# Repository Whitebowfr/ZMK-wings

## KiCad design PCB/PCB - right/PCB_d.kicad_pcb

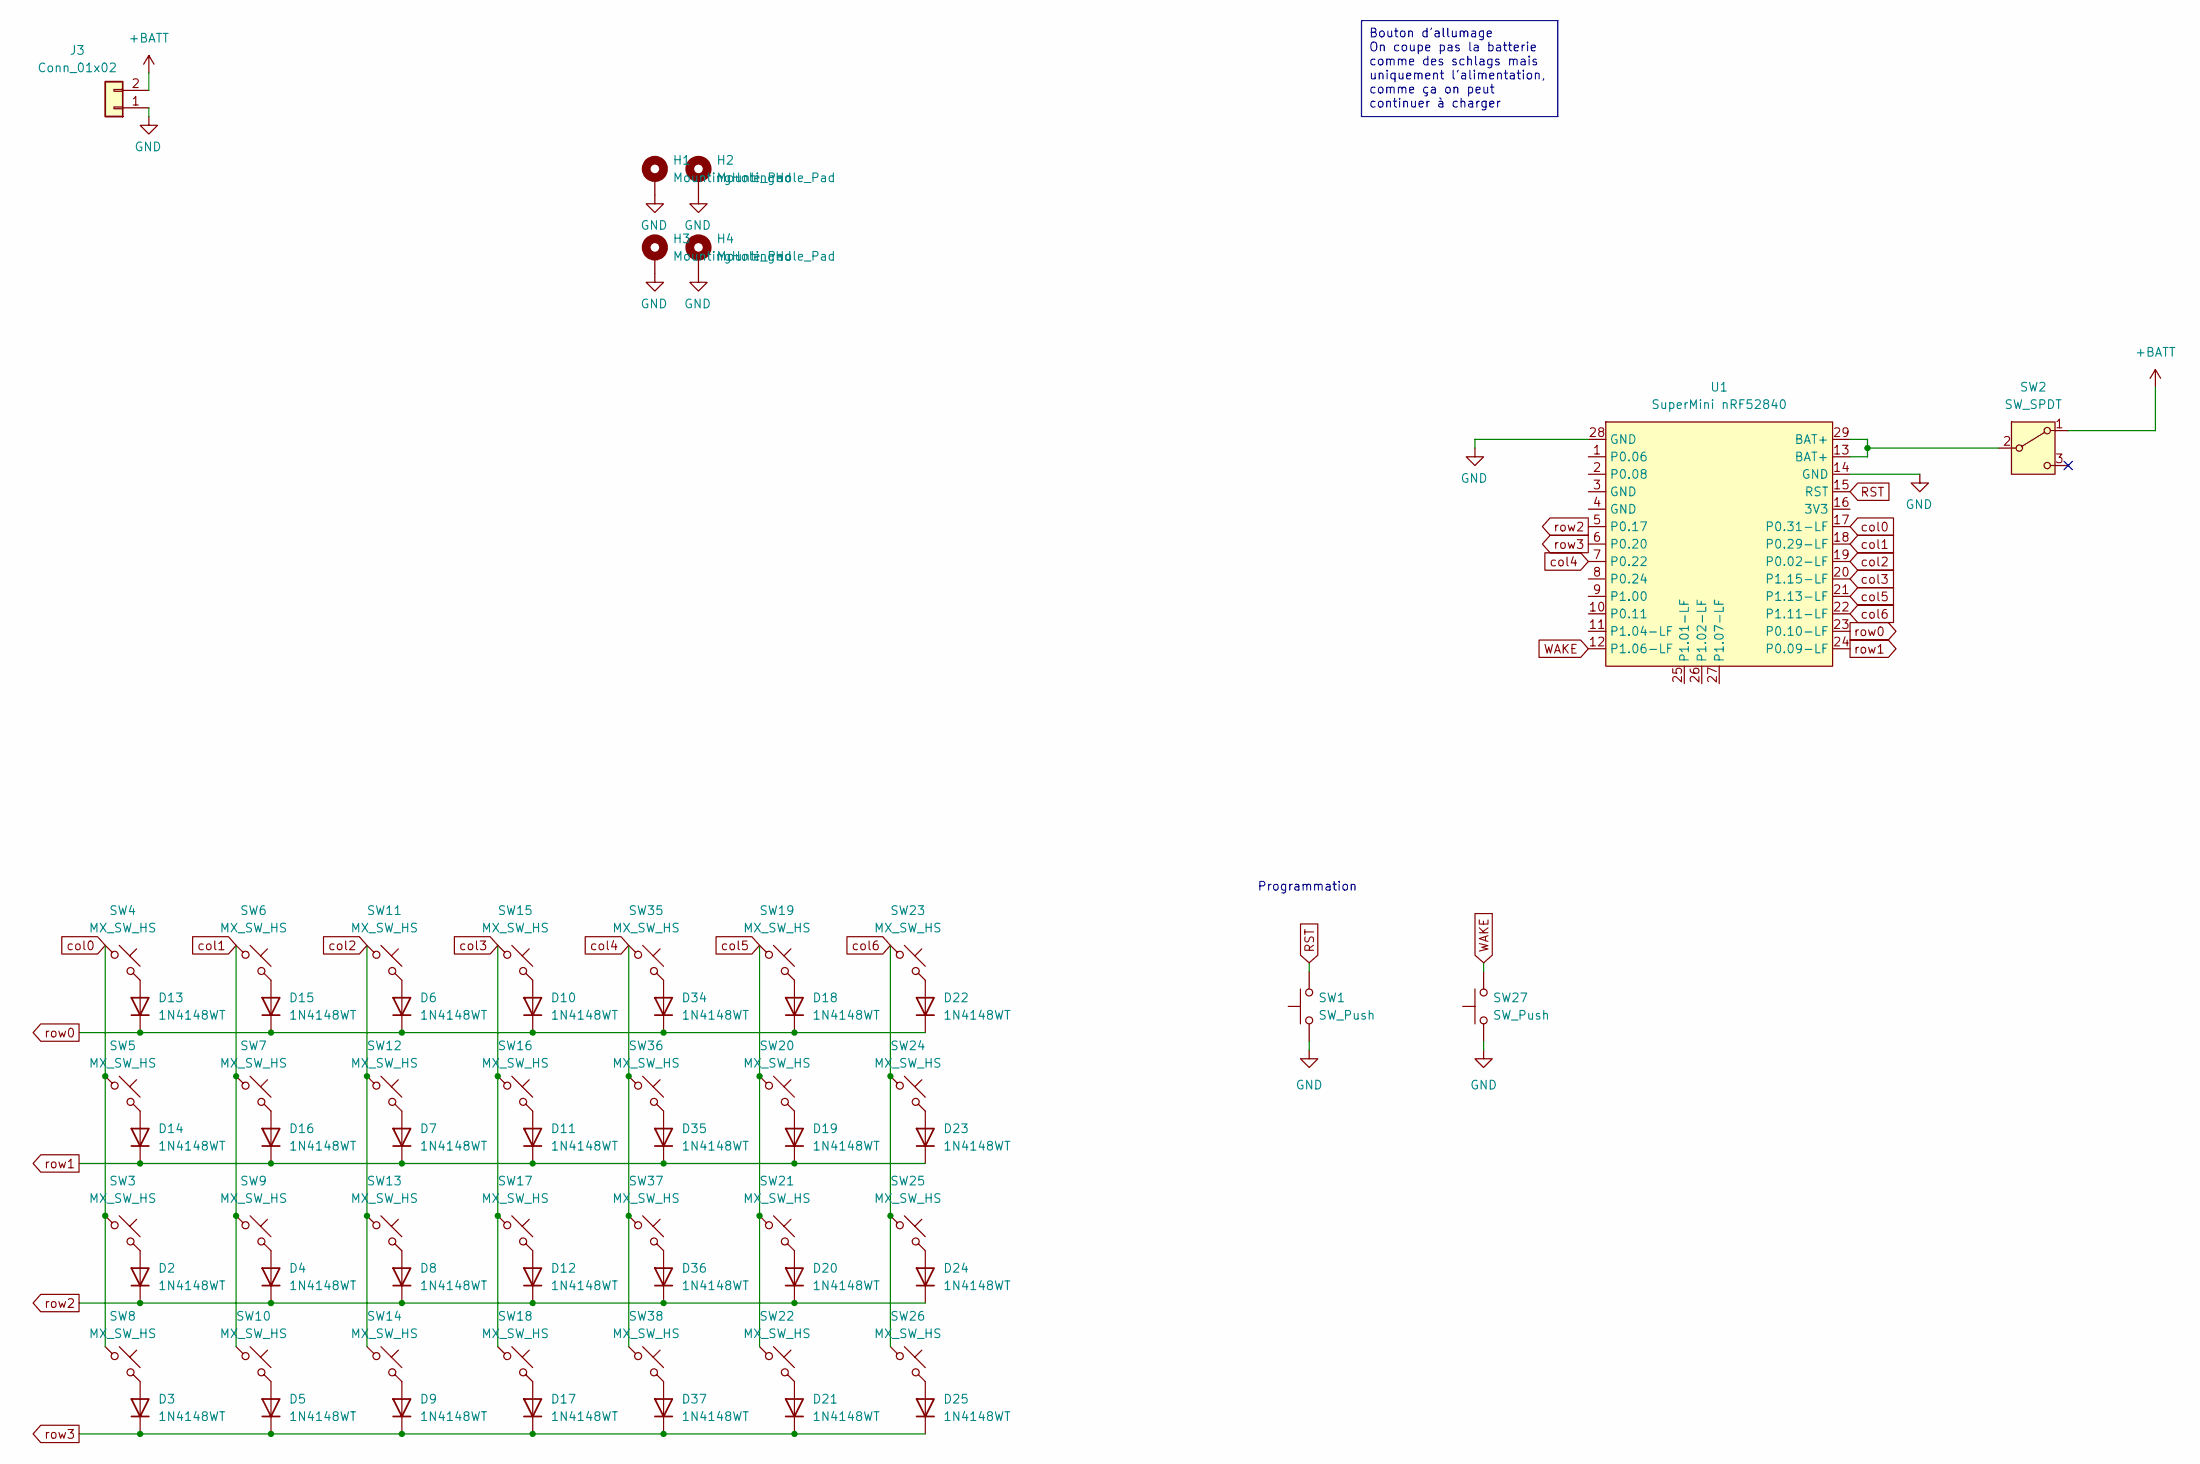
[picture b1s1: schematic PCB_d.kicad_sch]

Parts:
D2, D3, D4, D5, D6, D7, D8, D9, D10, D11, D12, D13, D14, D15, D16, D17, D18, D19, D20, D21, D22, D23, D24, D25, D34, D35, D36, D37: 1N4148WT; D_SOD-523
H1, H2, H3, H4: MountingHole_Pad; MountingHole_3.2mm_M3_ISO7380_Pad
J3: Conn_01x02; JST_XH_B2B-XH-AM_1x02_P2.50mm_Vertical
SW1, SW27: SW_Push; SW_PUSH_6mm_H5mm
SW2: SW_SPDT; SW_SPDT_PCM12
SW3, SW4, SW5, SW6, SW7, SW8, SW9, SW10, SW11, SW12, SW13, SW14, SW15, SW16, SW17, SW18, SW19, SW20, SW21, SW22, SW23, SW24, SW25, SW26, SW35, SW36, SW37, SW38: MX_SW_HS; SW_MX_HS_CPG151101S11_1u
U1: SuperMini nRF52840; SuperMini_nRF52840_AH_USBup

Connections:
+BATT: J3.2, SW2.1 (A)
GND: H1.1, H2.1, H3.1, H4.1, J3.1, SW1.1, SW27.1, U1.14 (GND), U1.28 (GND)
unnamed: D2.2 (A), SW3.2
unnamed: D3.2 (A), SW8.2
unnamed: D4.2 (A), SW9.2
unnamed: D5.2 (A), SW10.2
unnamed: D6.2 (A), SW11.2
unnamed: D7.2 (A), SW12.2
unnamed: D8.2 (A), SW13.2
unnamed: D9.2 (A), SW14.2
unnamed: D10.2 (A), SW15.2
unnamed: D11.2 (A), SW16.2
unnamed: D12.2 (A), SW17.2
unnamed: D13.2 (A), SW4.2
unnamed: D14.2 (A), SW5.2
unnamed: D15.2 (A), SW6.2
unnamed: D16.2 (A), SW7.2
unnamed: D17.2 (A), SW18.2
unnamed: D18.2 (A), SW19.2
unnamed: D19.2 (A), SW20.2
unnamed: D20.2 (A), SW21.2
unnamed: D21.2 (A), SW22.2
unnamed: D22.2 (A), SW23.2
unnamed: D23.2 (A), SW24.2
unnamed: D24.2 (A), SW25.2
unnamed: D25.2 (A), SW26.2
unnamed: D34.2 (A), SW35.2
unnamed: D35.2 (A), SW36.2
unnamed: D36.2 (A), SW37.2
unnamed: D37.2 (A), SW38.2
unnamed: SW2.2 (B), U1.13 (BAT+), U1.29 (BAT+)
RST: SW1.2, U1.15 (RST)
WAKE: SW27.2, U1.12 (P1.06-LF)
col0: SW3.1, SW4.1, SW5.1, SW8.1, U1.17 (P0.31-LF)
col1: SW6.1, SW7.1, SW9.1, SW10.1, U1.18 (P0.29-LF)
col2: SW11.1, SW12.1, SW13.1, SW14.1, U1.19 (P0.02-LF)
col3: SW15.1, SW16.1, SW17.1, SW18.1, U1.20 (P1.15-LF)
col4: SW35.1, SW36.1, SW37.1, SW38.1, U1.7 (P0.22)
col5: SW19.1, SW20.1, SW21.1, SW22.1, U1.21 (P1.13-LF)
col6: SW23.1, SW24.1, SW25.1, SW26.1, U1.22 (P1.11-LF)
row0: D6.1 (K), D10.1 (K), D13.1 (K), D15.1 (K), D18.1 (K), D22.1 (K), D34.1 (K), U1.23 (P0.10-LF)
row1: D7.1 (K), D11.1 (K), D14.1 (K), D16.1 (K), D19.1 (K), D23.1 (K), D35.1 (K), U1.24 (P0.09-LF)
row2: D2.1 (K), D4.1 (K), D8.1 (K), D12.1 (K), D20.1 (K), D24.1 (K), D36.1 (K), U1.5 (P0.17)
row3: D3.1 (K), D5.1 (K), D9.1 (K), D17.1 (K), D21.1 (K), D25.1 (K), D37.1 (K), U1.6 (P0.20)

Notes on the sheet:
Bouton d'allumage On coupe pas la batterie comme des schlags mais uniquement l'alimentation, comme ça on peut continuer à charger
Programmation

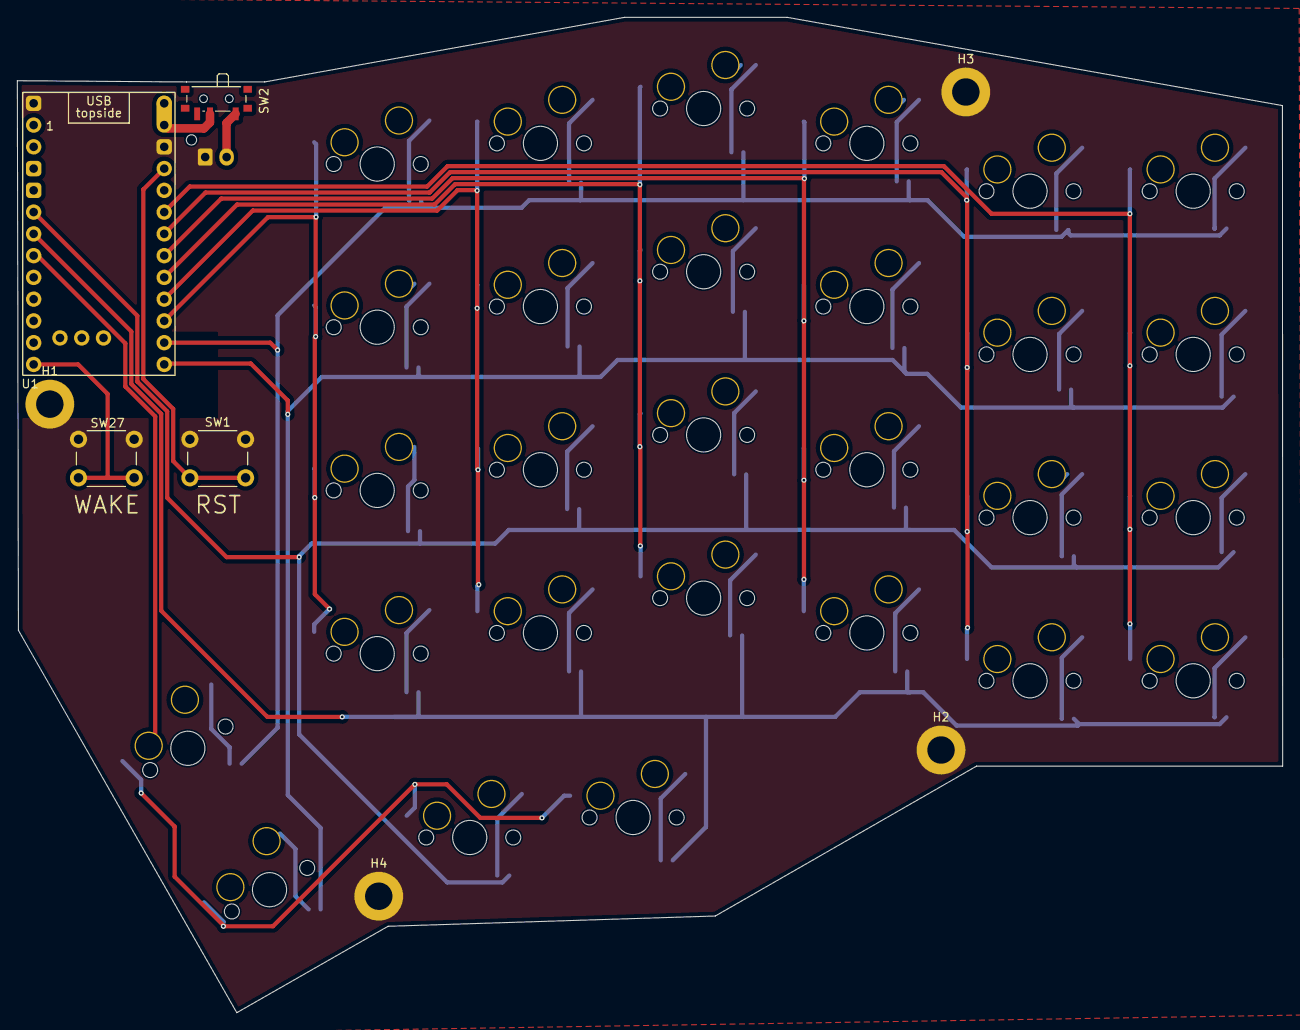
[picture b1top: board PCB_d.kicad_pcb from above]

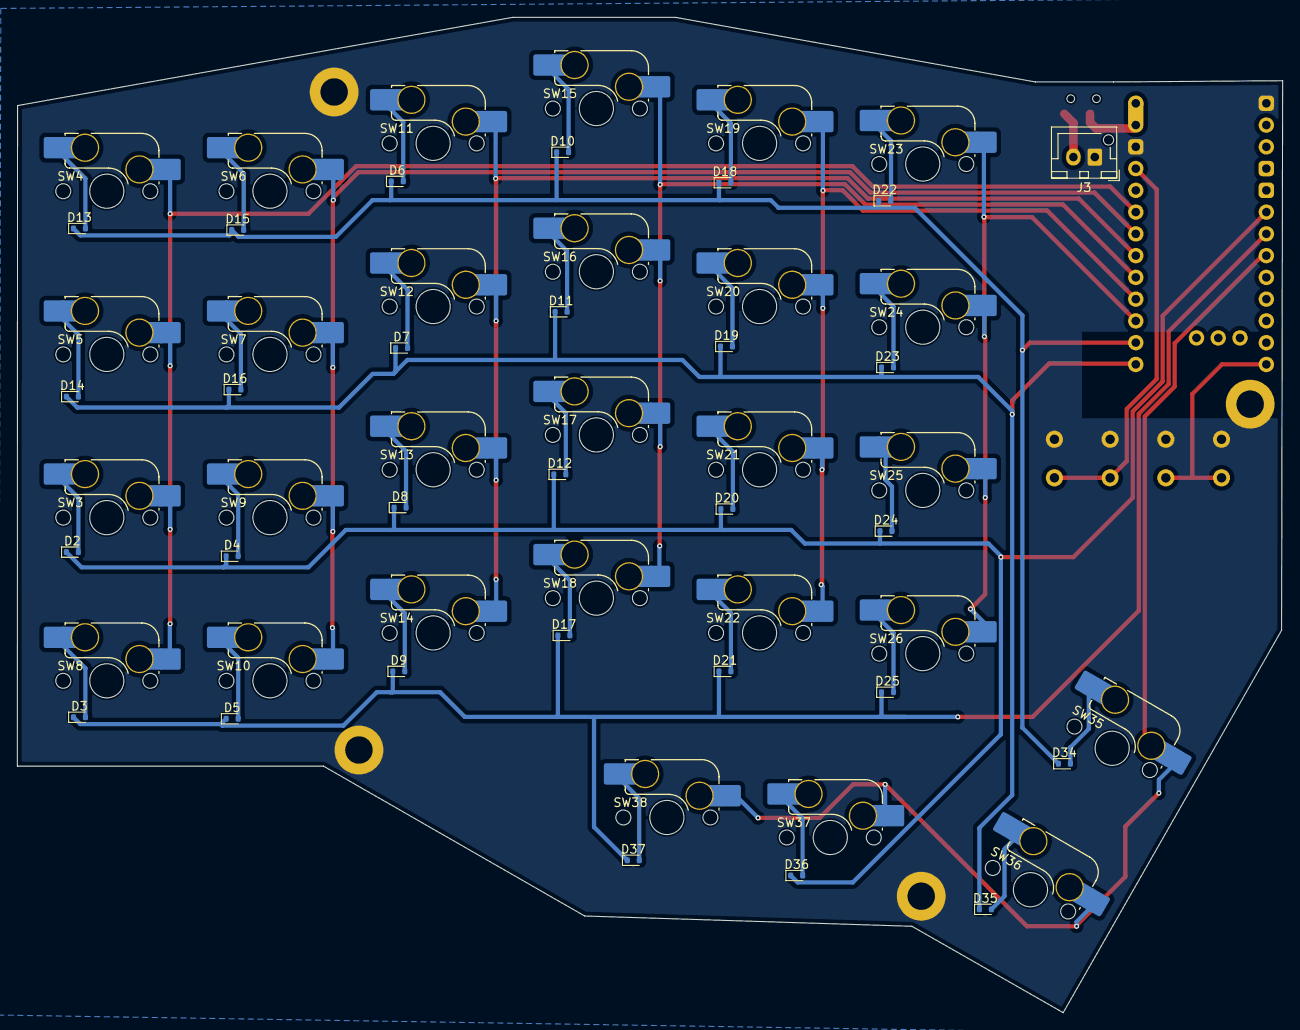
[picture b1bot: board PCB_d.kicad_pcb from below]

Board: 2 copper layers, 147.7 x 116.2 mm, 65 parts (57 on the bottom side), 44 nets.

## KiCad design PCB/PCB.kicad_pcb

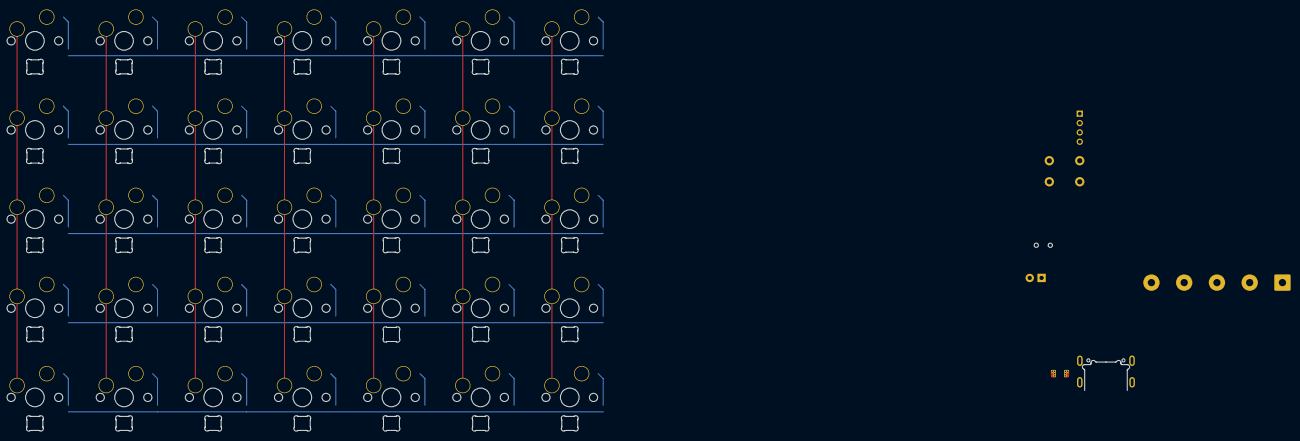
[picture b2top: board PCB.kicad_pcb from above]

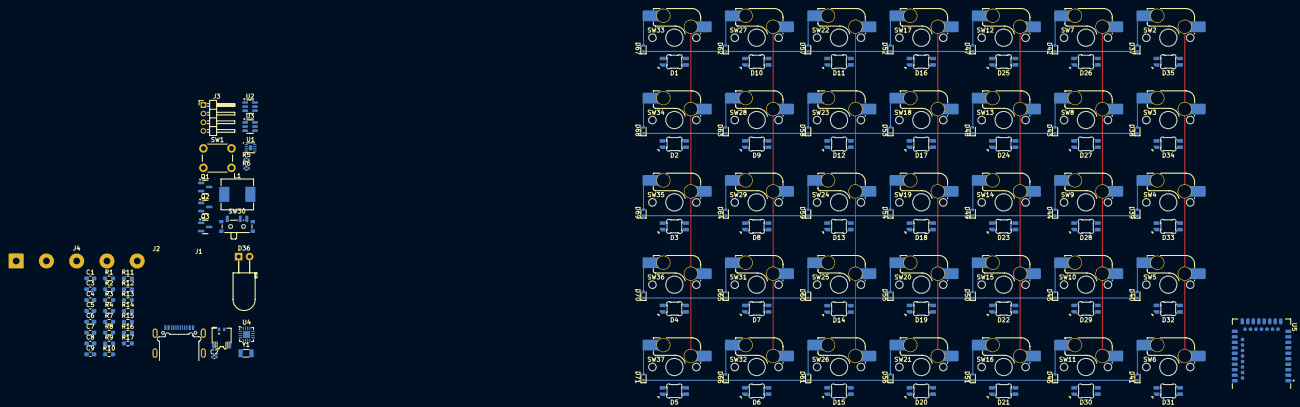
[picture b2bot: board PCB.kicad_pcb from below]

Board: 2 copper layers, 148 parts (148 on the bottom side), 118 nets.

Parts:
C1: 0.1uF; C_0603_1608Metric_Pad1.08x0.95mm_HandSolder
C2: 100n; C_0402_1005Metric
C3: 1uF; C_0603_1608Metric_Pad1.08x0.95mm_HandSolder
C4, C5, C6, C7: 4.7uF; C_0603_1608Metric_Pad1.08x0.95mm_HandSolder
C8, C9: 12pF; C_0603_1608Metric_Pad1.08x0.95mm_HandSolder
D1, D2, D3, D4, D5, D6, D7, D8, D9, D10, D11, D12, D13, D14, D15, D16, D17, D18, D19, D20, D21, D22, D23, D24, D25, D26, D27, D28, D29, D30, D31, D32, D33, D34, D35: WS2812B; LED_MX_6028R
D36: LED; LED_D5.0mm_Horizontal_O3.81mm_Z9.0mm
D37, D38, D39, D40, D41, D42, D43, D44, D45, D46, D47, D48, D49, D50, D51, D52, D53, D54, D55, D56, D57, D58, D59, D60, D61, D62, D63, D64, D65, D66, D67, D68, D69, D70, D71: 1N4148WT; D_SOD-523
J1: USB_C_Receptacle_USB2.0_16P; USB_C_Receptacle_HRO_TYPE-C-31-M-14
J2: Battery; Molex_Pico-EZmate_78171-0002_1x02-1MP_P1.20mm_Vertical
J3: Conn_01x04; PinHeader_1x04_P2.00mm_Horizontal
J4: Conn_01x05; SolderWire-0.75sqmm_1x05_P7mm_D1.25mm_OD3.5mm
L1: 10uH; L_Sunlord_MWSA0603S
Q1: AO3401A; SOT-23
Q2, Q3: 2N7002; SOT-23
R1, R2, R3, R4: 5.1k; R_0603_1608Metric_Pad0.98x0.95mm_HandSolder
R5: 100R; R_0402_1005Metric
R6: 1k; R_0402_1005Metric
R7: 1.5k; R_0603_1608Metric_Pad0.98x0.95mm_HandSolder
R8, R12, R14, R17: 10k; R_0603_1608Metric_Pad0.98x0.95mm_HandSolder
R9: 47k; R_0603_1608Metric_Pad0.98x0.95mm_HandSolder
R10: 1k; R_0603_1608Metric_Pad0.98x0.95mm_HandSolder
R11: 450; R_0603_1608Metric_Pad0.98x0.95mm_HandSolder
R13, R16: 100; R_0603_1608Metric_Pad0.98x0.95mm_HandSolder
R15: 100k; R_0603_1608Metric_Pad0.98x0.95mm_HandSolder
SW1: SW_Push; SW_PUSH_6mm_H5mm
SW2, SW3, SW4, SW5, SW6, SW7, SW8, SW9, SW10, SW11, SW12, SW13, SW14, SW15, SW16, SW17, SW18, SW19, SW20, SW21, SW22, SW23, SW24, SW25, SW26, SW27, SW28, SW29, SW31, SW32, SW33, SW34, SW35, SW36, SW37: MX_SW_HS; SW_MX_HS_CPG151101S11_1u
SW30: SW_SPDT; SW_SPDT_PCM12
U1: MAX17048; TDFN-8-1EP_2x2mm_P0.5mm_EP0.8x1.2mm
U2: DW01A; SOT-23-6
U3: FS8205; SOT-23-6
U4: BQ24075RGT; VQFN-16-1EP_3x3mm_P0.5mm_EP1.6x1.6mm
U5: nRF52840_E73-2G4M08S1C
Y1: 32.768 KHz; Crystal_SMD_3215-2Pin_3.2x1.5mm

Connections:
+3.3V: C6.2, J4.5, L1.2, R1.1, R2.1, U5.19 (VDD)
+5V: C3.2, J1.A4 (VBUS), J1.A9 (VBUS), J1.B4 (VBUS), J1.B9 (VBUS), J3.1, R16.1, U4.13 (IN), U5.27 (VBUS)
+BATT: C1.2, C5.2, J2.1, R5.1, R15.1, U1.2 (CELL), U1.3 (VDD), U4.2 (BAT), U4.3 (BAT)
+VSW: C4.2, C7.2, D36.2 (A), Q1.3 (D), R12.1, U4.6 (EN1), U4.10 (OUT), U4.11 (OUT), U5.23 (VDDH)
COUPLING_SENS: J3.2, U5.38 (P1.02)
D+: J1.A7 (D-), J1.B7 (D-), U5.31 (D+)
D-: J1.A6 (D+), J1.B6 (D+), U5.29 (D-)
EN_LED: R13.1, U5.6 (P1.13)
GND: C1.1, C3.1, C4.1, C5.1, C6.1, C7.1, C8.2, C9.2, D1.3 (VSS), D2.3 (VSS), D3.3 (VSS), D4.3 (VSS), D5.3 (VSS), D6.3 (VSS), D7.3 (VSS), D8.3 (VSS), D9.3 (VSS), D10.3 (VSS), D11.3 (VSS), D12.3 (VSS), D13.3 (VSS), D14.3 (VSS), D15.3 (VSS), D16.3 (VSS), D17.3 (VSS), D18.3 (VSS), D19.3 (VSS), D20.3 (VSS), D21.3 (VSS), D22.3 (VSS), D23.3 (VSS), D24.3 (VSS), D25.3 (VSS), D26.3 (VSS), D27.3 (VSS), D28.3 (VSS), D29.3 (VSS), D30.3 (VSS), D31.3 (VSS), D32.3 (VSS), D33.3 (VSS), D34.3 (VSS), D35.3 (VSS), J1.A1 (GND), J1.A12 (GND), J1.B1 (GND), J1.B12 (GND), J1.S1 (SHIELD), J2.MP (MountPin), J3.4, J4.1, Q2.2 (S), Q3.2 (S), R3.2, R4.2, R6.1, R8.2, R9.2, R10.2, R11.2, R14.2, R17.2, SW1.1, SW30.3 (C), U1.1 (CTG), U1.4 (GND), U1.6 (QSTRT), U1.9 (GND), U3.3 (S2), U4.4 (~CE), U4.5 (EN2), U4.8 (VSS), U4.17 (VSS), U5.5 (GND), U5.21 (GND), U5.24 (GND)
LED_SERIAL: D1.4 (DIN), U5.17 (P1.09)
unnamed: D1.2 (DOUT), D2.4 (DIN)
unnamed: D2.2 (DOUT), D3.4 (DIN)
unnamed: D3.2 (DOUT), D4.4 (DIN)
unnamed: D4.2 (DOUT), D5.4 (DIN)
unnamed: D5.2 (DOUT), D6.4 (DIN)
unnamed: D6.2 (DOUT), D7.4 (DIN)
unnamed: D8.4 (DIN), D9.2 (DOUT)
unnamed: D10.4 (DIN), D11.2 (DOUT)
unnamed: D9.4 (DIN), D10.2 (DOUT)
unnamed: D11.4 (DIN), D12.2 (DOUT)
unnamed: D12.4 (DIN), D13.2 (DOUT)
unnamed: D13.4 (DIN), D14.2 (DOUT)
unnamed: D7.2 (DOUT), D14.4 (DIN)
unnamed: D8.2 (DOUT), D15.4 (DIN)
unnamed: D15.2 (DOUT), D16.4 (DIN)
unnamed: D16.2 (DOUT), D17.4 (DIN)
unnamed: D17.2 (DOUT), D18.4 (DIN)
unnamed: D18.2 (DOUT), D19.4 (DIN)
unnamed: D19.2 (DOUT), D20.4 (DIN)
unnamed: D20.2 (DOUT), D21.4 (DIN)
unnamed: D21.2 (DOUT), D28.4 (DIN)
unnamed: D22.4 (DIN), D23.2 (DOUT)
unnamed: D22.2 (DOUT), D29.4 (DIN)
unnamed: D23.4 (DIN), D24.2 (DOUT)
unnamed: D24.4 (DIN), D25.2 (DOUT)
unnamed: D25.4 (DIN), D26.2 (DOUT)
unnamed: D26.4 (DIN), D27.2 (DOUT)
unnamed: D27.4 (DIN), D28.2 (DOUT)
unnamed: D29.2 (DOUT), D30.4 (DIN)
unnamed: D30.2 (DOUT), D31.4 (DIN)
unnamed: D31.2 (DOUT), D32.4 (DIN)
unnamed: D32.2 (DOUT), D33.4 (DIN)
unnamed: D33.2 (DOUT), D34.4 (DIN)
unnamed: D34.2 (DOUT), D35.4 (DIN)
unnamed: D36.1 (K), R7.1
unnamed: D37.2 (A), SW2.2
unnamed: D38.2 (A), SW3.2
unnamed: D39.2 (A), SW4.2
unnamed: D40.2 (A), SW5.2
unnamed: D41.2 (A), SW6.2
unnamed: D42.2 (A), SW7.2
unnamed: D43.2 (A), SW8.2
unnamed: D44.2 (A), SW9.2
unnamed: D45.2 (A), SW10.2
unnamed: D46.2 (A), SW11.2
unnamed: D47.2 (A), SW12.2
unnamed: D48.2 (A), SW13.2
unnamed: D49.2 (A), SW14.2
unnamed: D50.2 (A), SW15.2
unnamed: D51.2 (A), SW16.2
unnamed: D52.2 (A), SW17.2
unnamed: D53.2 (A), SW18.2
unnamed: D54.2 (A), SW19.2
unnamed: D55.2 (A), SW20.2
unnamed: D56.2 (A), SW21.2
unnamed: D57.2 (A), SW22.2
unnamed: D58.2 (A), SW23.2
unnamed: D59.2 (A), SW24.2
unnamed: D60.2 (A), SW25.2
unnamed: D61.2 (A), SW26.2
unnamed: D62.2 (A), SW27.2
unnamed: D63.2 (A), SW28.2
unnamed: D64.2 (A), SW29.2
unnamed: D65.2 (A), SW31.2
unnamed: D66.2 (A), SW32.2
unnamed: D67.2 (A), SW33.2
unnamed: D68.2 (A), SW34.2
unnamed: D69.2 (A), SW35.2
unnamed: D70.2 (A), SW36.2
unnamed: D71.2 (A), SW37.2
unnamed: J1.A5 (CC1), R4.1
unnamed: J1.B5 (CC2), R3.1
unnamed: C2.2, J2.2, U2.6 (VSS), U3.1 (S1)
unnamed: J4.2, U5.37 (SWDIO)
unnamed: J4.3, U5.39 (SWDCLK)
unnamed: Q1.1 (G), Q2.3 (D), R12.2
unnamed: Q2.1 (G), R13.2, R14.1
unnamed: Q3.1 (G), R16.2, R17.1
unnamed: R15.2, SW30.1 (A)
unnamed: R6.2, U2.2 (CSI)
unnamed: U2.3 (OC), U3.4 (G2)
unnamed: U2.1 (OD), U3.6 (G1)
unnamed: C2.1, R5.2, U2.5 (VDD)
unnamed: R10.1, U4.12 (ILIM)
unnamed: R11.1, U4.16 (ISET)
unnamed: R9.1, U4.14 (TMR)
unnamed: R8.1, U4.1 (TS)
unnamed: R7.2, U4.9 (~CHG)
unnamed: L1.1, U5.25 (DCCH)
unnamed: C8.1, U5.11 (P0.00/XL1), Y1.2
unnamed: C9.1, U5.13 (P0.01/XL2), Y1.1
PWR_CUT: D1.1 (VDD), D2.1 (VDD), D3.1 (VDD), D4.1 (VDD), D5.1 (VDD), D6.1 (VDD), D7.1 (VDD), D8.1 (VDD), D9.1 (VDD), D10.1 (VDD), D11.1 (VDD), D12.1 (VDD), D13.1 (VDD), D14.1 (VDD), D15.1 (VDD), D16.1 (VDD), D17.1 (VDD), D18.1 (VDD), D19.1 (VDD), D20.1 (VDD), D21.1 (VDD), D22.1 (VDD), D23.1 (VDD), D24.1 (VDD), D25.1 (VDD), D26.1 (VDD), D27.1 (VDD), D28.1 (VDD), D29.1 (VDD), D30.1 (VDD), D31.1 (VDD), D32.1 (VDD), D33.1 (VDD), D34.1 (VDD), D35.1 (VDD), Q1.2 (S)
RST: J4.4, SW1.2, U5.26 (P0.18/~RESET)
SCL: R2.2, U1.7 (SCL), U5.7 (P0.02/AIN0)
SDA: R1.2, U1.8 (SDA), U5.14 (P0.06)
SYSOFF: Q3.3 (D), SW30.2 (B), U4.15 (SYSOFF)
col0: SW2.1, SW3.1, SW4.1, SW5.1, SW6.1, U5.2 (P1.10)
col1: SW7.1, SW8.1, SW9.1, SW10.1, SW11.1, U5.1 (P1.11)
col2: SW12.1, SW13.1, SW14.1, SW15.1, SW16.1, U5.15 (P0.05/AIN3)
col3: SW17.1, SW18.1, SW19.1, SW20.1, SW21.1, U5.33 (P0.13)
col4: SW22.1, SW23.1, SW24.1, SW25.1, SW26.1, U5.35 (P0.24)
col5: SW27.1, SW28.1, SW29.1, SW31.1, SW32.1, U5.41 (P0.09/NFC1)
col6: SW33.1, SW34.1, SW35.1, SW36.1, SW37.1, U5.43 (P0.10/NFC2)
row0: D37.1 (K), D42.1 (K), D47.1 (K), D52.1 (K), D57.1 (K), D62.1 (K), D67.1 (K), U5.3 (P0.03/AIN1)
row1: D38.1 (K), D43.1 (K), D48.1 (K), D53.1 (K), D58.1 (K), D63.1 (K), D68.1 (K), U5.4 (P0.28/AIN4)
row2: D39.1 (K), D44.1 (K), D49.1 (K), D54.1 (K), D59.1 (K), D64.1 (K), D69.1 (K), U5.8 (P0.29/AIN5)
row3: D40.1 (K), D45.1 (K), D50.1 (K), D55.1 (K), D60.1 (K), D65.1 (K), D70.1 (K), U5.9 (P0.31/AIN7)
row4: D41.1 (K), D46.1 (K), D51.1 (K), D56.1 (K), D61.1 (K), D66.1 (K), D71.1 (K), U5.10 (P0.30/AIN6)

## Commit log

2024-07-07 temp
2024-07-08 init
2024-07-09 Added template
2024-07-09 added matrix
2024-07-09 Added circuit and started PCB
2024-07-26 Tried LEDs, too complicated
2025-02-14 Removed old PCB
2025-02-14 Removed backups ?
2025-02-14 Removed backups
2025-02-14 added config
2025-02-15 Moved stuff around for github actions build
2025-02-15 Fixed wrong board specified
2025-02-15 Fixed kscan matrix
2025-02-15 Added missing semicolumns
2025-02-15 Added missing semicolumns (again)
2025-02-15 Fixed soft-off
2025-02-16 Fixed soft-off (again)
2025-02-16 Fixed soft-off (again) (again)
2025-02-16 fixed keymap
